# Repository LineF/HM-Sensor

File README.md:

# HM-Sensor

Nachbau des "Universalsensors" von Dirk, allerdings mit anderen Sensoren.

Zum Einsatz kommen die günstigen DHT-22 und/oder DS18B20 Sensoren. 
Alternativ kann noch ein SHT-21 (sehr kompakt und genau) verwendet werden (Code hierfür allerdings nicht vorhanden)

Der Sensor verwendet als Untermodul die NewAskSin Library von Trilu. Diese habe ich für meine Bedürfnisse etwas angepaßt, wird aber zur Zeit regelmäßig mit Trilus Code aktualisiert.

**Anpassungen:**

 - Erweiterung für WeatherSensor Messages
 - weitere Verbesserungen beim Energieverbrauch
 - Stabilität beim Peering mit HM-CC-RT-DN verbessert
 - Einbau eines 32KHz Uhrenquarzes möglich - damit weitere Verbesserung der Übertragungsgenauigkeit zu einem HM-CC-RT-DN und weitere Reduktion des Stromverbrauchs
 - LED beim Senden kann abgeschaltet werden
 - OSCCAL-Register des Atmel kann remote eingestellt werden (damit kann auch ohne Quarz eine gute Genauigkeit der Taktfrequenz erreicht werden)
 - Automatische Watchdog-Kalibrierung
 - Serielle Debug-Ausgabe auf "flush" umgestellt; damit entfallen die teilweise eingebauten schlecht kalkulierbaren delays
 - Batteriemessgenauigkeit auf 1/100V erhöht (ich mag's halt genau)
 - HAVE_DATA Message-Verarbeitung: damit nimmt der Sensor auch ohne Drücken des Config-Buttons Befehle von der Zentrale bei der nächsten Temperaturübermittlung an
 - der eine oder andere Fix (teilweise von Trilu bereits eingebaut)

Schaltplan, Layout und Belichtungsplan gibt's im Unterordner Schematic.
Die erste Version wurde mit Eagle erstellt (Unterordner Eagle)
Da ich meine Platinen selber ätze, habe ich hier auf doppelseitiges Layout verzichtet - es gibt dafür ein paar Drahtbrücken.

Die zweite Version wurde mit KiCad erstellt und dann bei einem professionellen Fertiger gefertigt (Unterordner Kicad).
Da gibts auch die entsprechenden Bilder.

Achtung:
Die aktuelle Version ab Mitte Mai 2017 hat statt GDO0 jetzt GDO2 verbunden (Fehler beim Erstellen des Schaltplans).
Dies wurde aber im Communication-Modul bei den Parametern IOCFG0 und IOCFG2 entsprechend berücksichtigt.

Als Sendemodul kommt ein CC1101 auf einem günstigen Breakout-Board aus China zum Einsatz.

Entwicklungsumgebung: Atmel Studio 7.0

Der Branch "dev" ist mein aktueller Entwicklungszweig - die Version kann evtl. fehlerhaft oder gar nicht compilierbar sein.
Im Zweifelsfall bitte die Releases verwenden.

Das Release 2.0 ist das letzte stabile und basiert auf der neuen C++ Lib von Trilu (vielen Dank dafür!)

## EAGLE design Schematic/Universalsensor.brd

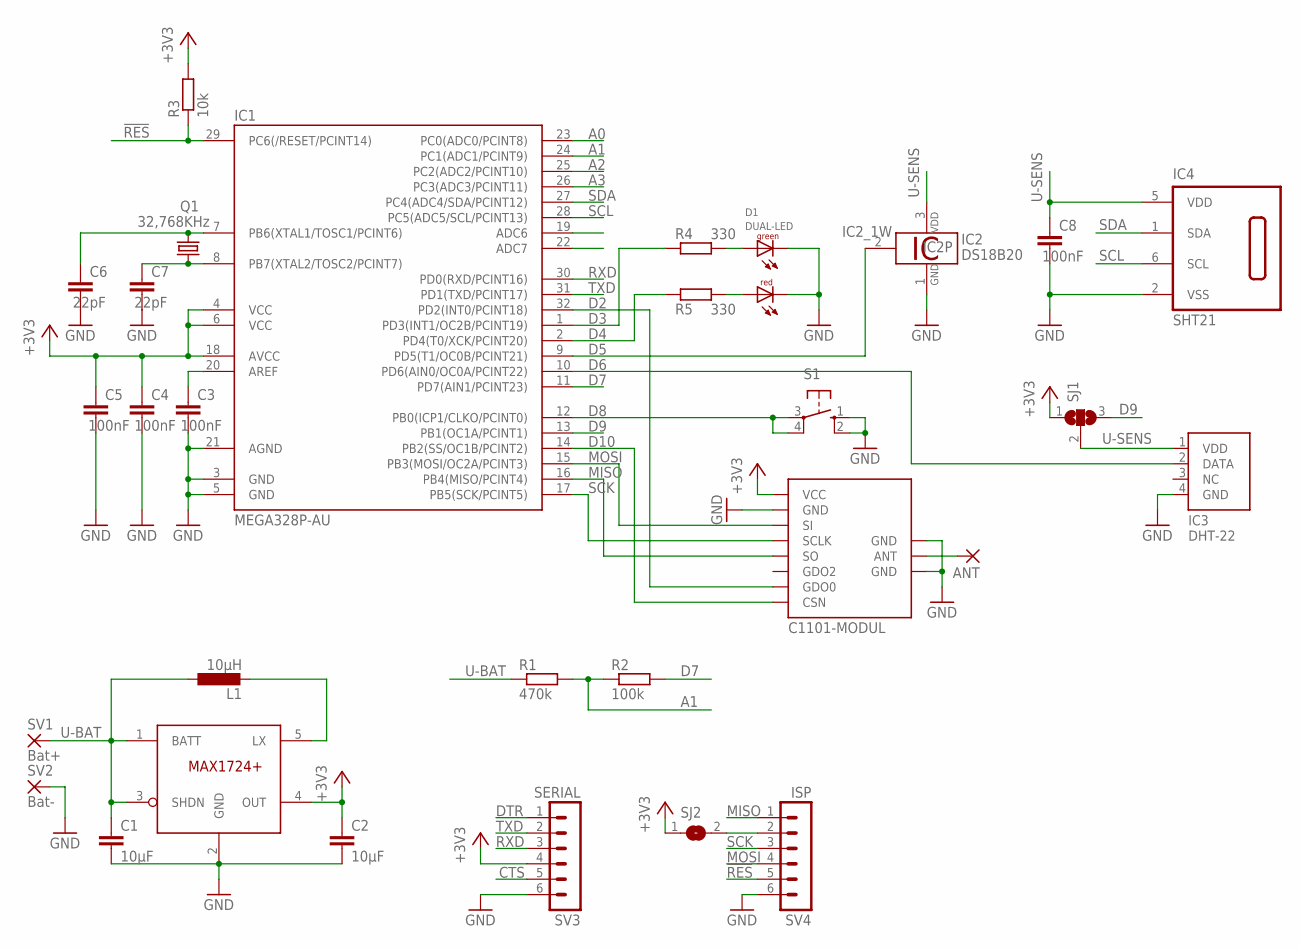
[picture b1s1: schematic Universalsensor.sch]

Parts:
ANT: 2,54/1,1
C1, C2: 10µF; C0603K
C3, C4, C5, C8: 100nF; C0603K
C6, C7: 22pF; C0603K
D1: DUAL-LED
IC1: MEGA328P-AU; TQFP32-08
IC2: DS18B20; TO92-
IC3: DHT-22; DHT-22-L
IC4: SHT21; DFN6/SHT
IC5: MAX1724; SOT23-5L
L1: 10µH; L3230M
Q1: 32,768KHz; OSCILLATOR_SMD
R1: 470k; R0805
R2: 100k; R0805
R3: 10k; R0805
R4, R5: 330; R0805
S1: 10-XX; B3F-10XX
SJ1: SJ2W; SJ_2
SJ2: SJ
SV1: Bat+; 2,54/1,1
SV2: Bat-; 2,54/1,1
SV3: SERIAL; MA06-1
SV4: ISP; MA06-1
U$2: C1101-MODUL; CC1101-MODUL

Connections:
!RES: IC1.29 (PC6(/RESET/PCINT14)), R3.1, SV4.5
+3V3: C2.1, C4.1, C5.1, IC1.4 (VCC), IC1.6 (VCC), IC1.18 (AVCC), IC5.4 (OUT), R3.2, SJ1.1, SJ2.1, SV3.4, U$2.VCC
A0: IC1.23 (PC0(ADC0/PCINT8))
A1: IC1.24 (PC1(ADC1/PCINT9)), R1.2, R2.1
A2: IC1.25 (PC2(ADC2/PCINT10))
A3: IC1.26 (PC3(ADC3/PCINT11))
CTS: SV3.5
D2: IC1.32 (PD2(INT0/PCINT18)), U$2.GDO0
D3: IC1.1 (PD3(INT1/OC2B/PCINT19)), R4.2
D4: IC1.2 (PD4(T0/XCK/PCINT20)), R5.2
D5: IC1.9 (PD5(T1/OC0B/PCINT21)), IC2.2 (1W)
D6: IC1.10 (PD6(AIN0/OC0A/PCINT22)), IC3.2 (DATA)
D7: IC1.11 (PD7(AIN1/PCINT23)), R2.2
D8: IC1.12 (PB0(ICP1/CLKO/PCINT0)), S1.3, S1.4 (P1)
D9: IC1.13 (PB1(OC1A/PCINT1)), SJ1.3
D10: IC1.14 (PB2(SS/OC1B/PCINT2)), U$2.CSN
DTR: SV3.1
GND: C1.2, C2.2, C3.2, C4.2, C5.2, C6.2, C7.2, C8.2, D1.P$3 (KG), D1.P$4 (KR), IC1.3 (GND), IC1.5 (GND), IC1.21 (AGND), IC2.1 (GND), IC3.4 (GND), IC4.2 (VSS), IC5.2 (GND), S1.1 (S), S1.2 (S1), SV2.1, SV3.6, SV4.6, U$2.GND@1 (GND), U$2.GND@2 (GND), U$2.GND@3 (GND)
MISO: IC1.16 (PB4(MISO/PCINT4)), SV4.1, U$2.SO
MOSI: IC1.15 (PB3(MOSI/OC2A/PCINT3)), SV4.4, U$2.SI
unnamed: IC5.5 (LX), L1.2
unnamed: C3.1, IC1.20 (AREF)
unnamed: C6.1, IC1.7 (PB6(XTAL1/TOSC1/PCINT6)), Q1.2
unnamed: D1.P$1 (AG), R4.1
unnamed: SJ2.2, SV4.2
unnamed: D1.P$2 (AR), R5.1
unnamed: C7.1, IC1.8 (PB7(XTAL2/TOSC2/PCINT7)), Q1.1
unnamed: ANT.1, U$2.ANT
RXD: IC1.30 (PD0(RXD/PCINT16)), SV3.3
SCK: IC1.17 (PB5(SCK/PCINT5)), SV4.3, U$2.SCLK
SCL: IC1.28 (PC5(ADC5/SCL/PCINT13)), IC4.6 (SCL)
SDA: IC1.27 (PC4(ADC4/SDA/PCINT12)), IC4.1 (SDA)
TXD: IC1.31 (PD1(TXD/PCINT17)), SV3.2
U-BAT: C1.1, IC5.1 (BATT), IC5.3 (SHDN), L1.1, R1.1, SV1.1
U-SENS: C8.1, IC2.3 (VDD), IC3.1 (VDD), IC4.5 (VDD), SJ1.2

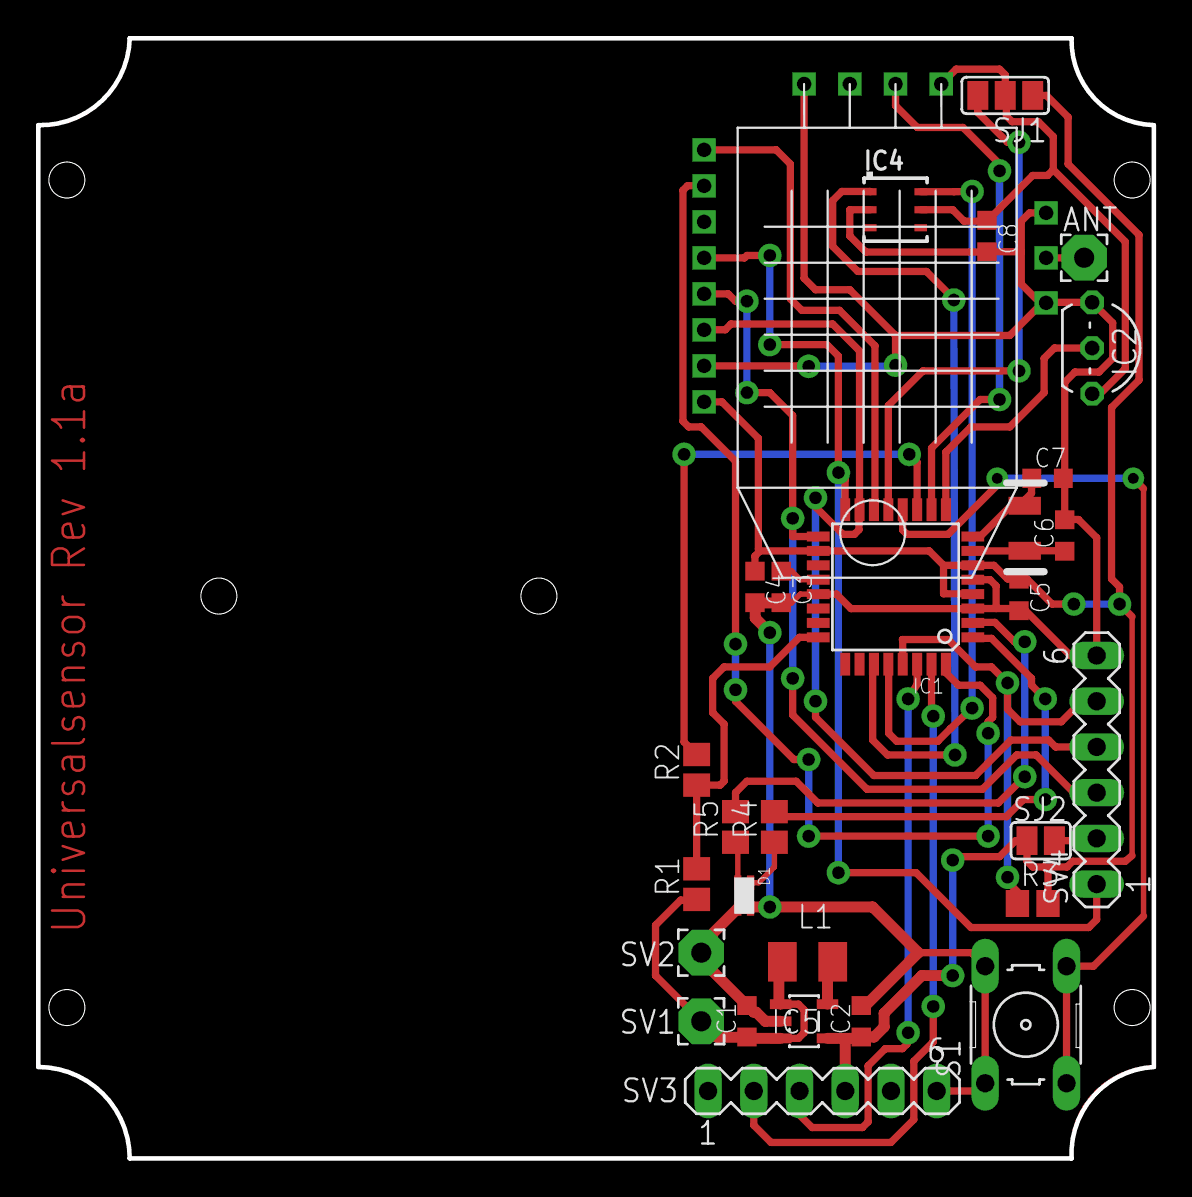
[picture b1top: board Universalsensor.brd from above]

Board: 2 copper layers, 62.0 x 62.2 mm, 30 parts (1 on the bottom side), 30 nets.

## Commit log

2016-06-09 adapt fhem config file
2016-06-17 get channel 0 registers running
2016-06-26 added subrepo NewAskSin, fix osccal settings
2016-06-28 more work
2016-07-07 more power savings
2016-07-07 ignore release directory
2016-07-08 use serial_flush
2016-07-08 added atmel studio project files
2016-07-19 more serial flush
2016-07-31 more schematic files added
2016-08-01 change in ee structure due to merge with DevAES fix index changes due to DevAES merge
2016-08-02 some cleanup
2016-08-02 changes due to new merge
2016-08-04 new submodule commit
2016-08-30 changes to get it compiled after merge
2016-09-01 change 8000ms sleep to 250ms sleep
2016-09-18 debug startup
2016-09-30 fix compilation errors
2016-10-01 first working compile with new cmTHSensWeather class
2016-10-06 more
2016-10-06 raise firmware level
2016-10-07 some work, but reading registers doesn't work
2016-10-08 fix minor typos, add extended debug console
2016-10-08 some small debug changes
2016-10-16 new schematic for low freq crystal oscillator and sht21
2016-10-19 modify chnl0 change notification
2016-10-20 new NewAskSin commit
2016-10-29 changes to support low frequency oscillator
2016-10-30 cosmetic changes and go back to TH1 values
2016-10-31 schematic changed - only one crystal load capacitor needed, crystal doc added
2016-10-31 a bit more debugging
2016-11-02 changed readme
2016-11-03 changes after merge
2016-11-03 new submodule id
2016-11-05 revert to 250ms mode
2016-11-28 some corrections
2016-12-05 file set changed
2016-12-26 fix compilation errors due to merge, fix project member files
2016-12-28 debug code now in extra module
2016-12-28 changes for new 32KHz code
2017-01-04 fix 85C and change in filenames
2017-01-14 change in file structure
2017-01-14 code compiling again after merge
2017-01-26 change file structure
2017-01-26 enable burstRX mode again
2017-02-09 some changes
2017-02-12 add configurable cyclicMessageOffset, r/o factory osccal and frequency test led
2017-02-16 change power_modes, change factOscCal handling, change debugging
2017-02-22 changes for new battery oversampling
2017-03-07 pins redefined, change bat measure time
2017-03-16 submodule commit changed
2017-03-28 add free_ram()
2017-03-28 change to refs
2017-04-22 added kicad schematic files
2017-04-22 pcb routing complete
2017-04-23 went to production
2017-04-26 better ground layout
2017-04-26 fix config_status_request
2017-05-11 change hmid and serial for new test device
2017-05-11 restructure schematic file tree, add pictures

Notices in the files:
parts and their libraries:
sensirion: Copyright (C) 2011, Bob Starr
